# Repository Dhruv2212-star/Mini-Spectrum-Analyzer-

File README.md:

**Ai ussage**- used to find correct parts for the build and help choose the correct MCU for this project & debugging the firmware and  STM32 **ONLY**.  

**Project Description**- The Mini Spectrum Analyzer is a compact electronic device designed to detect and display radio frequency (RF) signals over a selected frequency range. 

It uses an ADF4351 frequency synthesizer to generate a programmable local oscillator and an ADL5801 mixer to convert the received RF signal into an intermediate frequency.  

The AD8313 logarithmic detector measures the signal strength, while the STM32G031K8T6 microcontroller processes the data and displays the spectrum on an SPI TFT display.  

Power input- The device is powered through a USB-C connector and includes onboard power regulation, protection circuitry, user control buttons, status indicators for easy debugging.  

*Designed in Kicad 10.0.3 as 4 layered PCB with independent power planes such as GND & +3v3*

**Note to reviewer**- the Format of the Readme is kept in tabular manner to keep things organized and easy to read. instead of long para i have used tables which i created in excel and pasted it into git file;. if you do have any further question regarding to my project, feel free to reach out to me on slack where i can explain it to you if you want.  
**[slack id- U0AFT499S6S,  Magic tree/Dhruv Patel]**
------------------------------------------------------------------------------------------------------------------------------------------
# Firmware Flashing Guide  
Don't flash the ZIP directly, The ZIP contains the ADF4351 driver source, not a ready-to-flash .bin  
You first need an STM32 project that compiles it, Create the STM32 project In STM32CubeIDE, create a project for: STM32G031K8T6  
Then configure the pins to match our PCB 
The ADF4351 uses a 3-wire serial interface and accepts a programmable 35 MHz–4.4 GHz output range.  
Now *Configure SPI1  
In CubeMX the following:  
SPI1 → Master  
8-bit  
MSB first  
CPOL = Low  
CPHA = 1st Edge  
Software NSS  
Configure PA4, PA5 and PA7 for the SPI interface, with PA4 ultimately serving as the ADF4351 LE control  
Add the driver. From the ZIP, copy: adf4351.h, adf4351.c  

into your CubeIDE project:  
Core/Inc/adf4351.h  
Core/Src/adf4351.c  
Then copy the initialization from: Maine.c to main.c  
now, Set your actual reference  
Our PCB uses:  
Y1 = 10 MHz TCXO  
hz = 10000000UL  
The ADF4351's reference/PFD configuration is important because it directly affects the generated frequency.  
->Build the project  
In CubeIDE:  
Project → Build Project  

 If it has:  
0 errors  
0 warnings related to the driver, ONLY then proceed 

*Connect your ST-LIN  
Use your J4 SWD header:  
J4-1 > SWDIO  
J4-2 > SWCLK   
J4-3 > NRST  
J4-4 > +3V3 / VTREF  
J4-5 > GND  
First test: don't test the spectrum analyzer yet  

Connect the ST-LINK to your PC and open STM32CubeProgrammer. ST officially supports programming STM32 devices through ST-LINK/SWD, and CubeProgrammer can program and verify the MCU flash  
Click:  
ST-LINK > SWD > Connect  
If it detects your STM32G031, stop there and tell me that it connected successfully.  
**Then we'll flash it**  
Compile > generate .elf > flash > reset > verify ADF4351 lock > check RF output  

so the driver is configured for:  

| STM32 U5     | ADF4351 U3   |
| ------------ | ------------ |
| PA4 — pin 11 | LE — pin 3   |
| PA5 — pin 12 | CLK — pin 1  |
| PA7 — pin 14 | DATA — pin 2 |
| PB0 — pin 15 | CE — pin 4   |
| PA1 — pin 8  | LD — pin 25  |

------------------------------------------------------------------------------------------------------------------------------------------
# PCB component's Role in the circuit 
 # Block 1 — USB-C Power Input & Protection

 | Ref | Component        | Role in the Circuit    |                                                                                     
| --- | ---------------- | ----------------------------------------------------------------------------------------------------------------------------------------- |
| J1  | USB-C Receptacle | Receives 5 V power from a USB-C source and serves as the main power input to the spectrum analyzer.                                          |
| F1  | Polyfuse         | Protects the board from excessive current by disconnecting the supply during a fault and automatically resetting after the fault is removed. |
| D1  | TVS/ESD Diode    | Protects the USB power line against electrostatic discharge and voltage spikes that could damage sensitive components.                       |
| R1  | 5.1 kΩ           | USB-C CC1 pull-down resistor that identifies the board as a power sink.                                                                      |
| R2  | 5.1 kΩ           | USB-C CC2 pull-down resistor that enables correct cable orientation detection.                                                               |
| C1  | 10 µF            | Reduces low-frequency voltage ripple and provides energy storage during sudden load changes.                                                 |
| C2  | 100 nF           | Filters high-frequency noise on the incoming USB power line.                                                                                 |

# Block 2 — 5 V to 3.3 V Power Regulation

| Ref | Component       | Role in the Circuit                                                                         |
| --- | --------------- | ------------------------------------------------------------------------------------------- |
| U1  | 3.3 V Regulator | Converts the incoming 5 V supply into a stable 3.3 V rail for the digital and RF circuitry. |
| L1  | Ferrite Bead    | Suppresses high-frequency switching noise between the regulator and the clean 3.3 V rail.   |
| C3  | 10 µF           | Stabilizes the regulator input and output while improving transient response.               |
| C4  | 100 nF          | High-frequency bypass capacitor for the regulator output.                                   |
| C5  | 100 nF          | Additional local decoupling capacitor to maintain a clean supply.                           |

# Block 3 — RF Input & Signal Conditioning

| Ref | Component   | Role in the Circuit                                                       |
| --- | ----------- | ------------------------------------------------------------------------- |
| R6  | 10 Ω        | Provides input damping and limits RF transients entering the signal path. |
| R7  | 10 Ω        | Works with R6 to improve signal integrity and reduce ringing.             |
| C6  | 100 pF      | AC-couples the RF signal while blocking DC from reaching the mixer stage. |
| D2  | PESD5V0X1UL | Protects the RF input against electrostatic discharge events.             |

# Block 4 — RF Detector & Block 5 — Frequency Generation, Mixer & IF Stage  

| Ref    | Component             | Role in the Circuit                                                                   |
| ------ | --------------------- | ------------------------------------------------------------------------------------- |
| U2     | AD8313                | Converts the RF signal level into a proportional DC voltage that the MCU can measure. |
| C7–C10 | Decoupling Capacitors | Filter supply noise and maintain stable operation of the RF detector.                 |

| REf    | Component                        | Role in the Circuit                                                                                                  |
| ------- | -------------------------------- | -------------------------------------------------------------------------------------------------------------------- |
| U3      | ADF4351                          | Generates a programmable local oscillator signal used to sweep the analyzer across different frequencies.            |
| U4      | ADL5801                          | Mixes the incoming RF signal with the local oscillator to produce an intermediate-frequency signal.                  |
| Y1      | 10 MHz TCXO                      | Provides a highly stable reference clock for accurate frequency generation.                                          |
| T1      | ADT4-1T+ Transformer             | Converts the differential IF signal into the required form while providing impedance matching.                       |
| R11–R15 | Bias / PLL Resistors             | Set PLL operating conditions, bias RF outputs, and configure the frequency synthesizer.                              |
| C11–C22 | Coupling / Decoupling Capacitors | Provide AC coupling, supply filtering, RF bypassing, and PLL loop-filter functions required for stable RF operation. |

# Block 6 — MCU, Display & Programming & Block 7 — User Interface  

| Ref | Component             | Role in the Circuit                                                                                      |
| --- | --------------------- | ------------------------------------------------------------------------------------------------------------------------ |
| U5  | STM32G031K8T6         | Controls the analyzer, programs the synthesizer, samples detector data, processes measurements, and updates the display. |
| J3  | ST7789 Display Module | Displays the measured spectrum, menus, and analyzer information to the user.                                             |
| J4  | SWD Header            | Allows firmware programming and debugging of the microcontroller.                                                        |
| R16 | 10 kΩ                 | Pull-up resistor for the MCU reset pin, ensuring reliable startup.                                                       |
| C24 | 100 nF                | High-frequency bypass capacitor for the MCU supply.                                                                      |
| C25 | 4.7 µF                | Bulk decoupling capacitor that stabilizes the MCU power rail during rapid current changes.                               |

| Ref | Component   | Role in the Circuit                                      |
| --- | ----------- | -------------------------------------------------------- |
| SW1 | Push Button | Increases frequency or navigates upward through menus.   |
| SW2 | Push Button | Decreases frequency or navigates downward through menus. |
| SW3 | Push Button | Selects menu options and confirms user actions.          |
| R17 | 10 kΩ       | Pull-up resistor for SW1 input.                          |
| R18 | 10 kΩ       | Pull-up resistor for SW2 input.                          |
| R19 | 10 kΩ       | Pull-up resistor for SW3 input.                          |

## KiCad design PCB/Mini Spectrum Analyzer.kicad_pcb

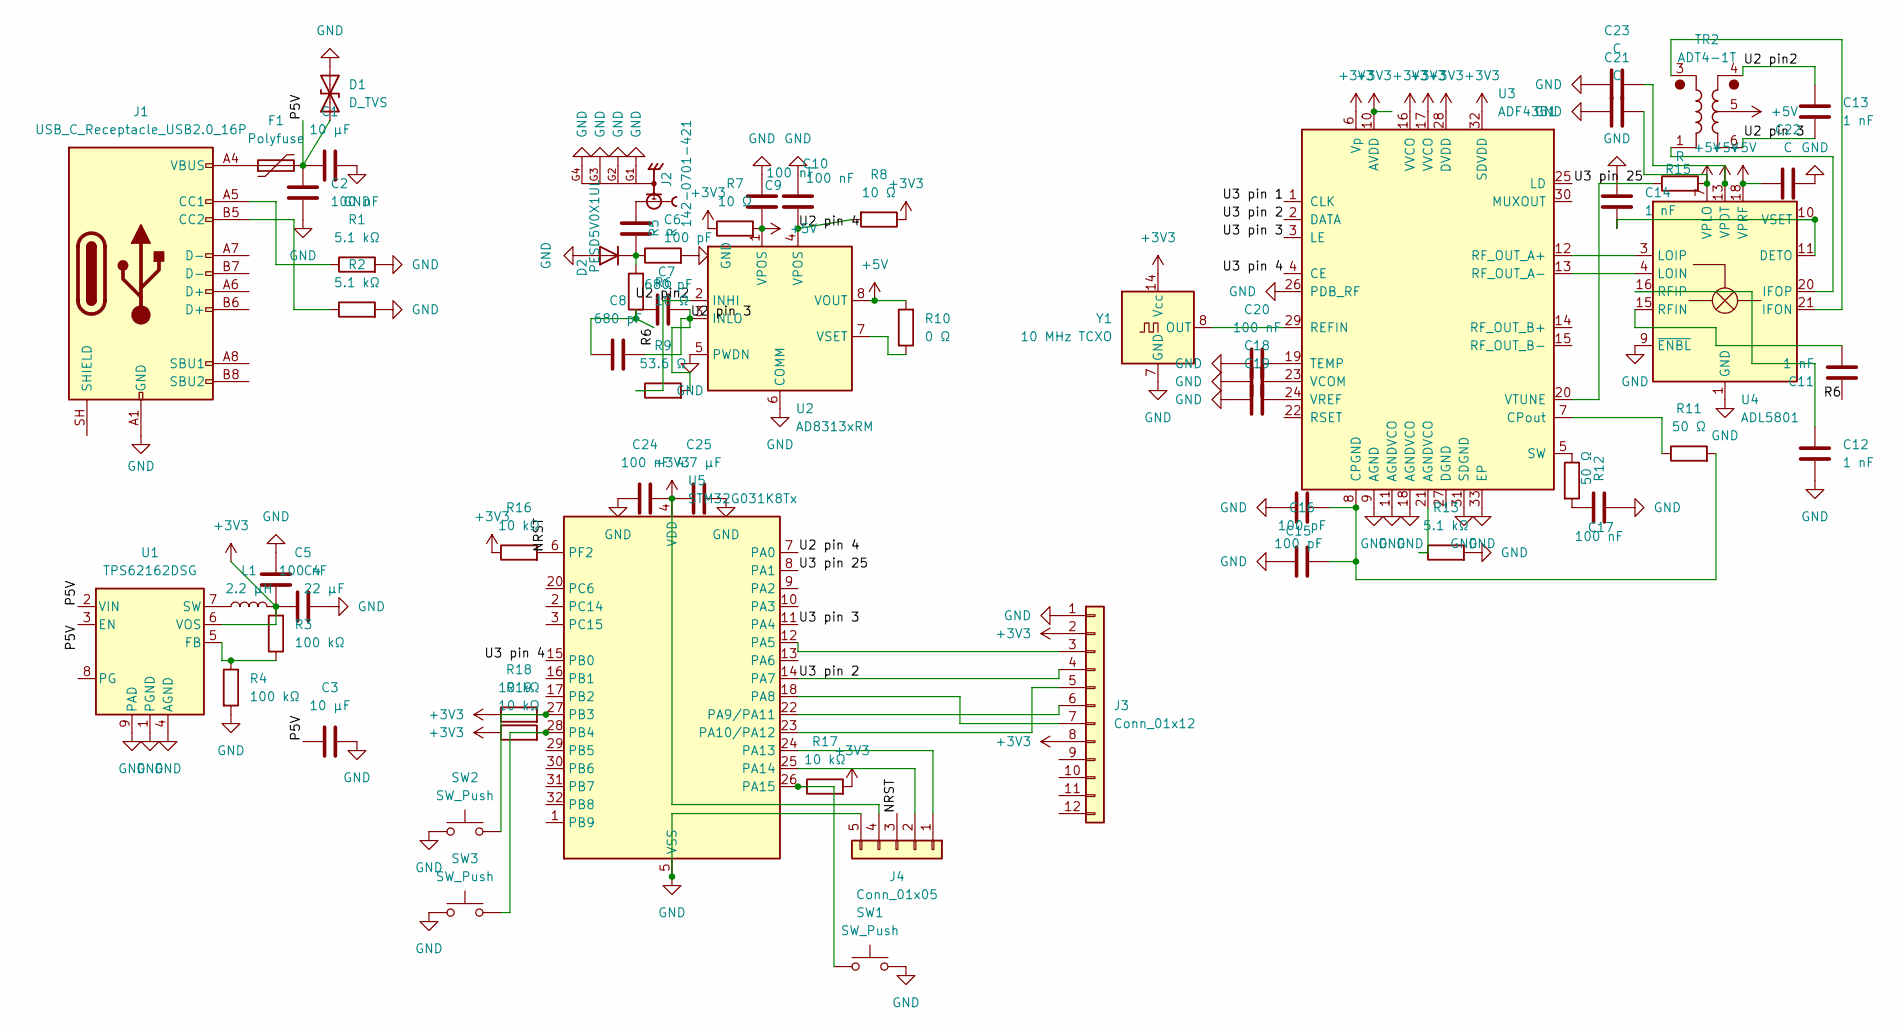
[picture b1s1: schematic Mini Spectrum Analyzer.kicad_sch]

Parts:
C1: 10 µF; C_1206_3216Metric
C2, C5, C9, C10, C17, C20, C24: 100 nF; C_0603_1608Metric
C3: 10 µF; C_0805_2012Metric
C4: 22 µF; C_0805_2012Metric
C6, C15, C16: 100 pF; C_0603_1608Metric
C7, C8: 680 pF; C_0603_1608Metric
C11, C12, C13, C14: 1 nF; C_0603_1608Metric
C18, C19: C_0603_1608Metric
C21, C22, C23: C; C_0603_1608Metric
C25: 4.7 µF; C_0603_1608Metric
D1: D_TVS; D_SMB
D2: PESD5V0X1UL; D_SOD-523
F1: Polyfuse; Fuse_1206_3216Metric
J1: USB_C_Receptacle_USB2.0_16P; USB_C_Receptacle_GCT_USB4105-xx-A_16P_TopMnt_Horizontal
J2: 142-0701-421; CINCH_142-0701-421; PARTREV 1a
J3: Conn_01x12; PinHeader_1x12_P2.54mm_Vertical
J4: Conn_01x05; PinHeader_1x05_P2.54mm_Vertical
L1: 2.2 µH; L_1210_3225Metric
R1, R2, R13: 5.1 kΩ; R_0603_1608Metric
R3, R4: 100 kΩ; R_0603_1608Metric
R5, R15: R; R_0603_1608Metric
R6, R7, R8: 10 Ω; R_0603_1608Metric
R9: 53.6 Ω; R_0603_1608Metric
R10: 0 Ω; R_0603_1608Metric
R11, R12: 50 Ω; R_0603_1608Metric
R16, R17, R18, R19: 10 kΩ; R_0603_1608Metric
SW1, SW2, SW3: SW_Push; SW_SPST_SKQG_WithoutStem
TR2: ADT4-1T; Mini-Circuits_CD542_H2.84mm
U1: TPS62162DSG; WSON-8-1EP_2x2mm_P0.5mm_EP0.9x1.6mm_ThermalVias
U2: AD8313xRM; MSOP-8_3x3mm_P0.65mm
U3: ADF4351; LFCSP-32-1EP_5x5mm_P0.5mm_EP3.25x3.25mm
U4: ADL5801; LFCSP-VQ-24-1EP_4x4mm_P0.5mm_EP2.642x2.642mm
U5: STM32G031K8Tx; LQFP-32_7x7mm_P0.8mm
Y1: 10 MHz TCXO; Oscillator_DIP-14

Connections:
+3V3: C4.2, C5.1, C24.2, C25.1, J3.2, J3.8, J4.4, L1.2, R3.2, R7.1, R8.1, R16.1, R17.2, R18.1, R19.1, U1.6 (VOS), U3.6 (Vp), U3.10 (AVDD), U3.16 (VVCO), U3.17 (VVCO), U3.28 (DVDD), U3.32 (SDVDD), U5.4 (VDD), Y1.14 (Vcc)
+5V: C9.2, C21.2, C22.1, C23.2, R7.2, R10.2, R15.2, TR2.5, U2.1 (VPOS), U2.8 (VOUT), U4.7 (VPLO), U4.13 (VPDT), U4.18 (VPRF), U4.24 (VPLO)
/NRST: J4.3, R16.2, U5.6 (PF2)
/P5V: C1.1, C2.1, C3.1, D1.1 (A1), F1.2, U1.2 (VIN), U1.3 (EN)
/R6: C7.1, C8.1, C11.1, R6.1
/U2 pin2: C13.1, R9.1, TR2.4, U2.2 (INHI)
/U2 pin 3: C7.2, C8.2, C13.2, R9.2, TR2.6, U2.3 (INLO)
/U2 pin 4: C10.2, R8.2, U2.4 (VPOS), U5.7 (PA0)
/U3 pin 1: U3.1 (CLK)
/U3 pin 2: J3.4, U3.2 (DATA), U5.14 (PA7)
/U3 pin 3: U3.3 (LE), U5.11 (PA4)
/U3 pin 4: U3.4 (CE), U5.15 (PB0)
/U3 pin 25: U5.8 (PA1)
GND: C1.2, C2.2, C3.2, C4.1, C5.2, C9.1, C10.1, C12.2, C14.1, C15.1, C16.1, C17.2, C18.1, C19.1, C20.1, C21.1, C22.2, C23.1, C24.1, C25.2, D1.2 (A2), D2.2 (A), J1.A1 (GND), J1.A12 (GND), J1.B1 (GND), J1.B12 (GND), J2.G1, J2.G2, J2.G3, J2.G4, J3.1, J4.5, R1.2, R2.2, R4.2, R5.2, R13.2, SW1.2, SW2.1, SW3.1, U1.1 (PGND), U1.4 (AGND), U1.9 (PAD), U2.5 (PWDN), U2.6 (COMM), U3.9 (AGND), U3.11 (AGNDVCO), U3.18 (AGNDVCO), U3.26 (PDB_RF), U3.31 (SDGND), U3.33 (EP), U4.1 (GND), U4.2 (GND), U4.5 (GND), U4.6 (GND), U4.8 (GND), U4.9 (~ENBL), U4.12 (GND), U4.14 (GND), U4.17 (GND), U4.19 (GND), U4.23 (GND), U4.25 (GND), U5.5 (VSS), Y1.7 (GND)
unnamed: C6.2, J2.1
unnamed: C17.1, R12.2
unnamed: C6.1, D2.1 (K), R5.1, R6.2
unnamed: F1.1, J1.A4 (VBUS), J1.A9 (VBUS), J1.B4 (VBUS), J1.B9 (VBUS)
unnamed: J1.A5 (CC1), R1.1
unnamed: J1.B5 (CC2), R2.1
unnamed: J3.3, U5.12 (PA5)
unnamed: J3.5, U5.23 (PA10/PA12)
unnamed: J3.6, U5.22 (PA9/PA11)
unnamed: J3.7, U5.18 (PA8)
unnamed: J4.1, U5.24 (PA13)
unnamed: J4.2, U5.25 (PA14)
unnamed: R13.1, U3.21 (AGNDVCO)
unnamed: R3.1, R4.1, U1.5 (FB)
unnamed: L1.1, U1.7 (SW)
unnamed: R10.1, U2.7 (VSET)
unnamed: C15.2, C16.2, R11.2, U3.8 (CPGND)
unnamed: R11.1, U3.7 (CPout)
unnamed: U3.29 (REFIN), Y1.8 (OUT)
unnamed: U3.12 (RF_OUT_A+), U4.3 (LOIP)
unnamed: U3.13 (RF_OUT_A-), U4.4 (LOIN)
unnamed: R12.1, U3.5 (SW)
unnamed: C20.2, U3.19 (TEMP)
unnamed: C18.2, U3.23 (VCOM)
unnamed: C19.2, U3.24 (VREF)
unnamed: R15.1, U3.20 (VTUNE)
unnamed: C14.2, U4.10 (VSET), U4.11 (DETO)
unnamed: TR2.3, U4.21 (IFON)
unnamed: TR2.1, U4.20 (IFOP)
unnamed: C11.2, U4.15 (RFIN)
unnamed: C12.1, U4.16 (RFIP)
unnamed: R17.1, SW1.1, U5.26 (PA15)
unnamed: R18.2, SW2.2, U5.27 (PB3)
unnamed: R19.2, SW3.2, U5.28 (PB4)

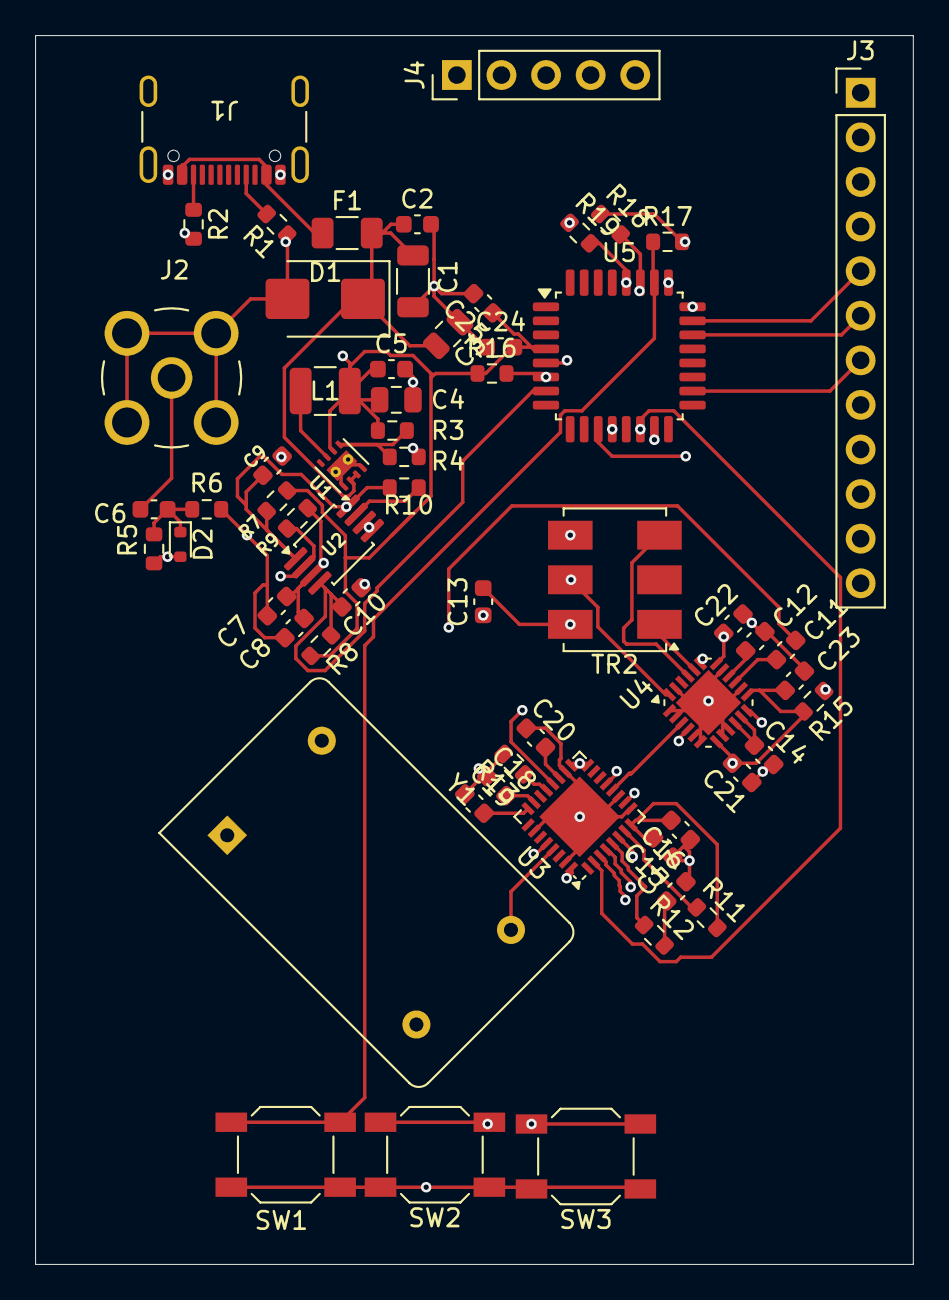
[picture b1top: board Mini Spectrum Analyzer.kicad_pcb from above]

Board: 4 copper layers, 50.0 x 70.0 mm, 61 parts (0 on the bottom side), 46 nets.
